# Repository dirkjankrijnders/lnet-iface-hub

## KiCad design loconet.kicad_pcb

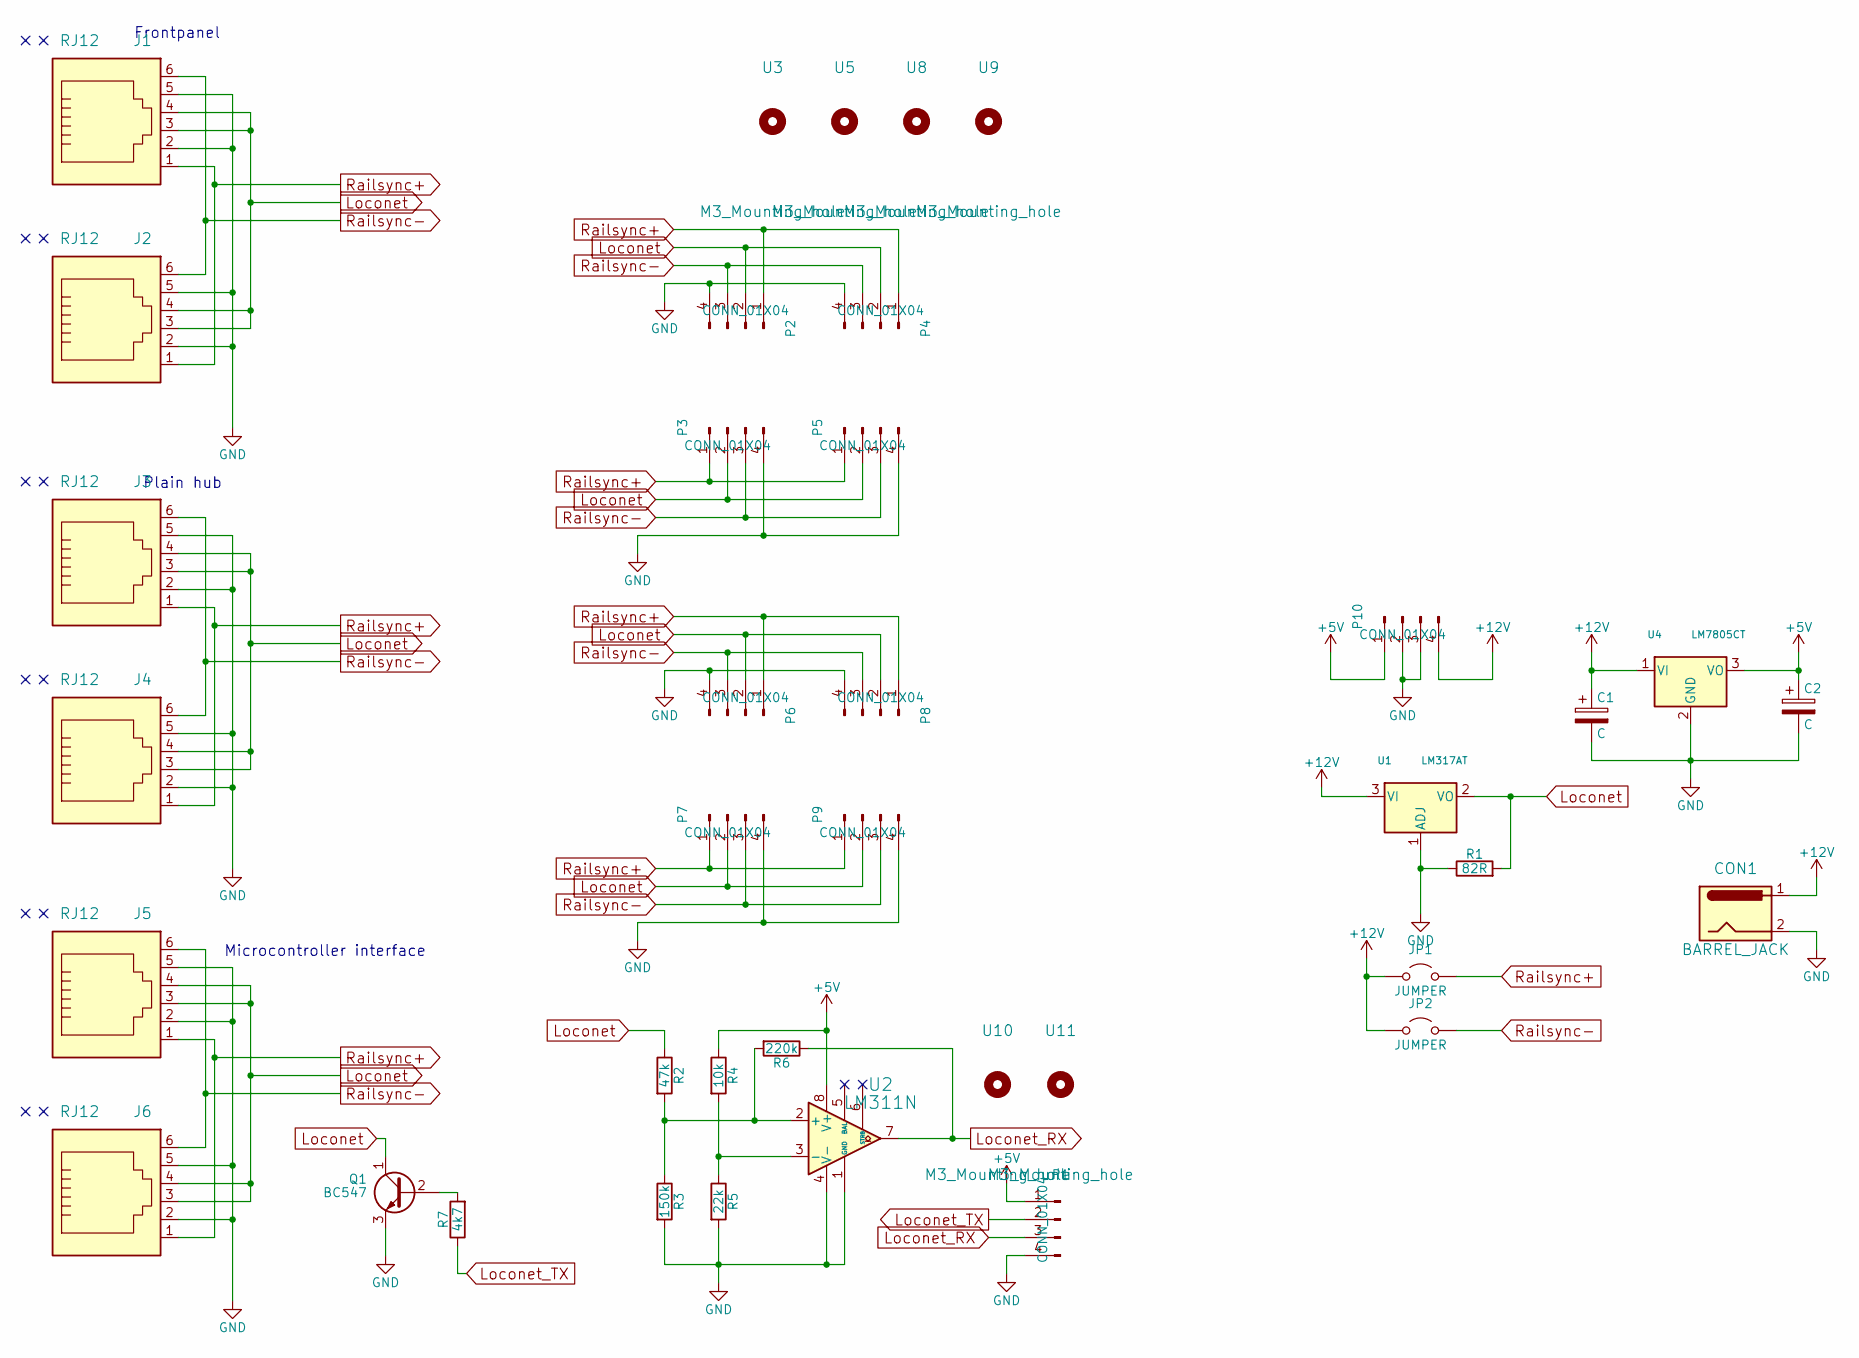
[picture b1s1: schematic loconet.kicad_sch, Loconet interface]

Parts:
C1, C2: C; C_Rect_L7.0mm_W6.0mm_P5.00mm
CON1: BARREL_JACK; BarrelJack_Horizontal
J1, J2, J3, J4, J5, J6: RJ12; RJ12_Amphenol_54601-x06_Horizontal
JP1, JP2: JUMPER; PinHeader_1x02_P2.54mm_Vertical
P1, P3, P5, P7, P9: CONN_01X04; PinSocket_1x04_P2.54mm_Horizontal
P2, P4, P6, P8, P10: CONN_01X04; PinHeader_1x04_P2.54mm_Horizontal
Q1: BC547; TO-92_Inline
R1: 82R; R_Axial_DIN0207_L6.3mm_D2.5mm_P7.62mm_Horizontal
R2: 47k; R_Axial_DIN0207_L6.3mm_D2.5mm_P7.62mm_Horizontal
R3: 150k; R_Axial_DIN0207_L6.3mm_D2.5mm_P7.62mm_Horizontal
R4: 10k; R_Axial_DIN0207_L6.3mm_D2.5mm_P7.62mm_Horizontal
R5: 22k; R_Axial_DIN0207_L6.3mm_D2.5mm_P7.62mm_Horizontal
R6: 220k; R_Axial_DIN0207_L6.3mm_D2.5mm_P7.62mm_Horizontal
R7: 4k7; R_Axial_DIN0207_L6.3mm_D2.5mm_P7.62mm_Horizontal
U1: LM317AT; TO-220-3_Vertical
U2: LM311N; DIP-8_W7.62mm
U3, U5, U8, U9, U10, U11: M3_Mounting_hole; MountingHole_3.2mm_M3_DIN965
U4: LM7805CT; TO-220-3_Vertical

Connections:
+5V: C2.1, P1.1, P10.1, R4.1, U2.8 (V+), U4.3 (VO)
+12V: C1.1, CON1.1, JP1.1 (A), JP2.1 (A), P10.4, U1.3 (VI), U4.1 (VI)
GND: C1.2, C2.2, CON1.2, J1.2, J1.5, J2.2, J2.5, J3.2, J3.5, J4.2, J4.5, J5.2, J5.5, J6.2, J6.5, P1.4, P2.4, P3.4, P4.4, P5.4, P6.4, P7.4, P8.4, P9.4, P10.2, P10.3, Q1.3 (E), R1.1, R3.2, R5.2, U1.1 (ADJ), U2.1 (GND), U2.4 (V-), U4.2 (GND)
Loconet: J1.3, J1.4, J2.3, J2.4, J3.3, J3.4, J4.3, J4.4, J5.3, J5.4, J6.3, J6.4, P2.2, P3.2, P4.2, P5.2, P6.2, P7.2, P8.2, P9.2, Q1.1 (C), R1.2, R2.1, U1.2 (VO)
Loconet_RX: P1.3, R6.1, U2.7
Loconet_TX: P1.2, R7.1
unnamed: Q1.2 (B), R7.2
unnamed: R2.2, R3.1, R6.2, U2.2 (+)
unnamed: R4.2, R5.1, U2.3 (-)
Railsync+: J1.1, J2.1, J3.1, J4.1, J5.1, J6.1, JP1.2 (B), P2.1, P3.1, P4.1, P5.1, P6.1, P7.1, P8.1, P9.1
Railsync-: J1.6, J2.6, J3.6, J4.6, J5.6, J6.6, JP2.2 (B), P2.3, P3.3, P4.3, P5.3, P6.3, P7.3, P8.3, P9.3

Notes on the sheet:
Microcontroller interface
Plain hub
Frontpanel

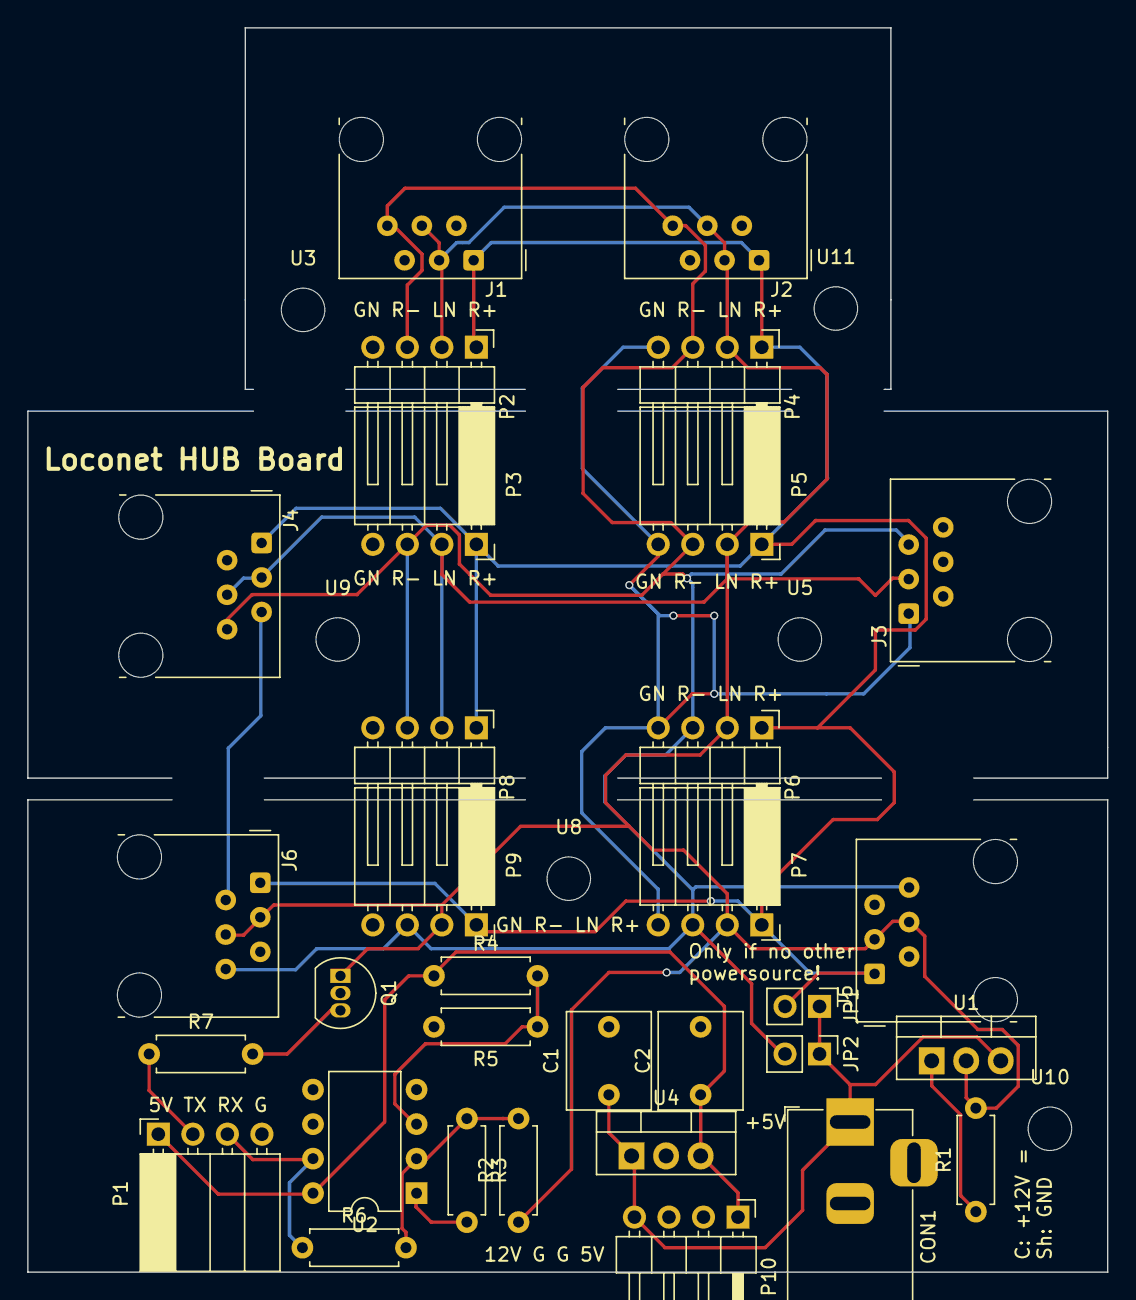
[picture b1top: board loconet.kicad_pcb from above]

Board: 2 copper layers, 79.4 x 91.6 mm, 38 parts (0 on the bottom side), 11 nets.

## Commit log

2015-05-26 Initial commit of design files
2015-05-26 Added main PCB
2015-05-26 Ignore backup and 3D files
2015-05-26 Added github links to every module
2015-05-26 3D impression from kicad
2015-05-26 Rev. 0 as send to dirtyPCB
2015-06-27 Fixed LM317 footprint
2015-08-28 Fixed the "pull-up" on the loconet line
    It was taken from the wrong pin of the LM317
2018-02-03 Updates to the 4.0.7 standard libraries
2018-02-03 Updated footprints to 4.0.7 standards
2018-02-03 Small fixes
2025-05-07 Started update to kicad 8
